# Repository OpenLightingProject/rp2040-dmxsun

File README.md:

# rp2040-dmxsun: A USB-DMX device based on RaspberryPi's RP2040 micro-controller with modular hardware

## What is it?

The rp2040-dmxsun is a multi-purpose DMX-512-A toolbox to control stage lighting systems. It's most common use-case is to transmit the DMX data generated on a PC, Raspberry Pi or similar in a format that the lighting fixtures on stage can understand. In the most simple case, it's an USB-DMX interface.

DMX-512-A works in networks called universes and each universe can contain up to 512 slots of data. dmxsun can transmit up to 16 universes, meaning you can control 8192 slots of DMX data at the same time.

Dmxsun is usually connected to its host via a single USB connection that also powers the device.
To the computer, the dmxsun device looks like a network card (it uses the CDC NCM interface) and the integrated DHCP-server assigns an IP-address to the host machine so they can talk to each other.

To find out dmxsun's IP address, have a look at your kernel log on Linux (run `dmesg`) or hover over the `Disconnect USB device` icon in Window's task bar or check the network device properties on macOS.

You can browse to this IP address in your web browser to access the integrated web server or you can send ArtNet or E1.31/sACN packets to the IP address to make dmxsun send this data as DMX data.

Furthermore, you can attach an nRF24 radio module to the base board to send or receive up to 4 universes wirelessly to or from another dmxsun device. That also means that the device can also work stand-alone, receiving DMX data from another dmxsun device and outputting it on local ports.

## Why is it called dmxsun?

The idea came when thinking about a suitable icon for the pages on the integrated web server. You can think about the dmxsun as being a central device and 16 rays of light coming out of it.

**Sun** could also be seen as an acronym for **s**ixteen **un**iverses :D

Maybe it's also because outdoor lighting technicians absolutely love the sun since they can perfectly set up their light show while the sun is shining bright ;)

## What does it look like?

The hardware consists of a base board into which the Raspberry Pi Pico-board plugs in to. To get a quick overview of the board's status, 8 RGB status LEDs are attached to the base board.

Attached to this base board can be 0 to 4 IO boards that carry the actual RS-485 drivers and XLR connectors:

If all 4 IO boards are attached to the base board, you can have 16 output ports fitting into 1U of an 19" rack:

## How is configuration data handled?

The complete configuration of the device, including IP address, patching and wireless configuration can be stored on any of the IO boards or on the base board.

When the device powers up, it scans the 4 IO board slots in order for connected boards and the configuration stored on them. As soon as a valid and non-disabled configuration is found, it is loaded and used. If no IO board has a valid configuration, it tries to load the config from the flash memory of the Pico board. If this also doesn't seem valid, a fallback configuration is applied.

The status LEDs on the base board indicate which IO boards have a valid configuration and which configuration is currently active.

All the configurations can be managed via the integrated web server.

## Where can I buy it?

Short answer: You can't. There is not (yet) a ready-made piece of hardware that can be bought and is ready to use. However, you are invited to build your own. Read on ;)

Longer answer: JLCPCB or a similar PCB factory. The schematics and PCB layout files are in the `hardware` folder (KiCad format) and you can send them to any PCB fab to have it produced for you. Then it's a bit of soldering on your side, plugging in a RaspberryPi Pico board and you're good to go.

If you just want to have a brief look at the schematics without cloning the repo and opening the files in KiCad, take a look at the kicad-export action: https://github.com/OpenLightingProject/rp2040-dmxsun/actions/workflows/kicad-exports.yml. It will generate a zip-archive containing all sort of PDFs.

**!!! Upcoming, incompatible hardware change: In the current schematics, we are using 256 byte large I2C-EEPROMs to store personality and configuration data. With the release of the Pico W and the need to store WiFi SSIDs and passwords, this will no longer be enough and the EEPROMs should provide 4096 byte in the future !!!**

## How can I try it out without spending much?

Very good question! All you need is a RaspberryPi Pico board, a microUSB cable and a PC, Laptop or RaspberryPi. You won't be able to actually control lighting fixtures, but you can get an idea of how this project works.

* Download the latest `UF2`-file (for example from here: https://github.com/OpenLightingProject/rp2040-dmxsun/actions/workflows/pico-build.yml) and flash it to your Pico board (see above)
* Wait until the board has rebooted and your PC has finished setting up the emulated network connection
* Find out the dmxsun's IP address as described in the [What is it?](#what-is-it)-section
* Open your web browser, browse to the IP address. You should see a web page with status information
* Using the navigation bar at the top, browse to `Console` and start changing values. Or fire up your favourite lighting control software (such as OLA or QLC+), configure it to send ArtNet or E1.31/sACN to the dmxsun's IP address and watch the values change in your web browser. It might seem laggy but that's only because the web interface only updates every second.
* If you're curious and have such devices, connect a logic analyzer or RS-485 driver to GPIOs 6 to 21. Those are the pins where the DMX data comes out. If you attach an RS-485-driver to one of those, you can also attach and control real fixtures.

## How do I compile the firmware?

If you just want to get started quickly find the most recent action run from the branch you're interested in, extract the attached artifact zip file (from https://github.com/OpenLightingProject/rp2040-dmxsun/actions/workflows/pico-build.yml ) and copy the rp2040-dmxsun.uf2 file to the Pico board when it's in bootloader mode.

Since this is a project that adheres to the guidelines set by Raspberry Pi for its pico-sdk (hopefully), you are best off following the detailed documentation at https://datasheets.raspberrypi.com/pico/getting-started-with-pico.pdf.

The build process will also build the React App for the integrated Web UI. For this to work, you will need to have NodeJS 14+ and NPM installed. React and all other JavaScript dependencies will be downloaded during the build, so make sure you are connected to the Internet.

With all dependencies installed, the following steps should suffice (example is for Linux, might differ for other OS):
```
git clone --recursive https://github.com/OpenLightingProject/rp2040-dmxsun.git
cd rp2040-dmxsun
mkdir build
cd build
cmake ..
make -j$(($(nproc)+1))
```
This should result in an `.uf2`-file being generated that you can flash to your Pico-board as described in Raspberry Pi's documentation.

**If you are seeing build errors, please make sure you are using pcio-sdk v1.5.0 (released 2023-02-11)**

## How does the data flow internally?

Dmxsun uses a pretty flexible architecture, consisting of mainly 24 DMX buffers acting as the main data storage. Data can come in via USB (either via the emulated Ethernet or some other, emulated protocol), wirelessly via the nRF24 module or from one input port and is then, depending on "patching" stored in one or more DMX buffers.

From there, again depending on "patching", the data is sent to one or more of the local DMX ports, to the nRF24 wireless module or to the host PC via Art-Net or E1.31/sACN.

The patching is currently fixed but will be made fully configurable in the future. The current patching works like this: Universes 1-16 from USB or emulated Ethernet go to internal DMX buffers 1-16 which go to the 16 local DMX ports. Additionally, the first 4 universes are also broadcast via the nRF24 module, should one be connected. Data coming in via the wireless module is sent to DMX buffers 5-8 and will as such appear on the local DMX ports 5-8.

## What are the upcoming features?

The best overview of planned features is to have a look at the GitHub issues: https://github.com/OpenLightingProject/rp2040-dmxsun/issues.

Since the hardware is modular, we do have the option to also support DMX input (currently work-in-progress) or universes with RDM support. There would also be the possibility to drive up to 6 WS2812b-based LED-strings instead of conventional DMX-512-A right off the board.

For the wireless part, mesh support is planned so you can add additional nodes forwarding the data when the wireless range is insufficient. It would also be great if we could talk to other, existing wireless DMX systems.

What might also help to make it easier to use is if dmxsun could emulate other, existing, USB DMX dongles. Then, it could also be used with other software that is not able to send Art-Net or E1.31/sACN but supports other dongles. The disadvantage here is that only a few dongles support more than 4 universes, while dmxsun supports 16.

As said above, the internal patching is hardcoded and cannot be changed by the user. This will change in the future, so that the current patching can be seen and changed in the integrated web interface.

## How is the project licensed?

This source code, schematics and board layouts is licensed under the Apache-2.0 license.

Parts of the original example code (`stdio_usb.*`, ...) is:

     * Copyright (c) 2020 Raspberry Pi (Trading) Ltd.
     * SPDX-License-Identifier: BSD-3-Clause

Parts taken and modified from TinyUSB (`tusb_config.h`, `usb_descriptors.c`) is:

     * The MIT License (MIT)
     * Copyright (c) 2019 Ha Thach (tinyusb.org)

This project proudly uses the following libraries and thanks the respective developers for their amazing work:
* [jsoncpp](https://github.com/open-source-parsers/jsoncpp), MIT license
* [libb64](https://github.com/libb64/libb64), Public domain
* [lwIP](https://savannah.nongnu.org/projects/lwip/), Modified BSD License
* [Pico-DMX](https://github.com/jostlowe/Pico-DMX), BSD 3-Clause "New" or "Revised" License
* [RF24, RF24Network and RF24Mesh](https://github.com/nRF24/RF24), GPL-2.0. Since this is not compatible with our Apache-2.0 license, this dependency will be removed in the future. dmxsun was GPL-licensed in the past
* [snappy](https://github.com/google/snappy), The 3-Clause BSD License

And for the integrated Web UI:
* [React](https://reactjs.org/), MIT license
* [Bootstrap](https://getbootstrap.com/), MIT license
* [Chart.js](https://www.chartjs.org/), MIT license
* [couch64](https://www.npmjs.com/package/couch64), CC-BY-SA
* [snappyjs](https://github.com/zhipeng-jia/snappyjs), MIT license
* [react-input-slider](https://github.com/swiftcarrot/react-input-slider), MIT license

## What else do I need to know?

If you attach an nRF24-board, you yourself are responsible to make sure you don't violate any local laws or regulations. Not all channels and transmit powers that the nRF24 module can use may be allowed to be used in your area. The Open Lighting Project cannot be held responsible should you break the law by using this project's hardware and/or software. Also, we did not run any EMC tests on the hardware. It might not be legal to operate the board without FCC, CE or similar certification, depending on where you live.

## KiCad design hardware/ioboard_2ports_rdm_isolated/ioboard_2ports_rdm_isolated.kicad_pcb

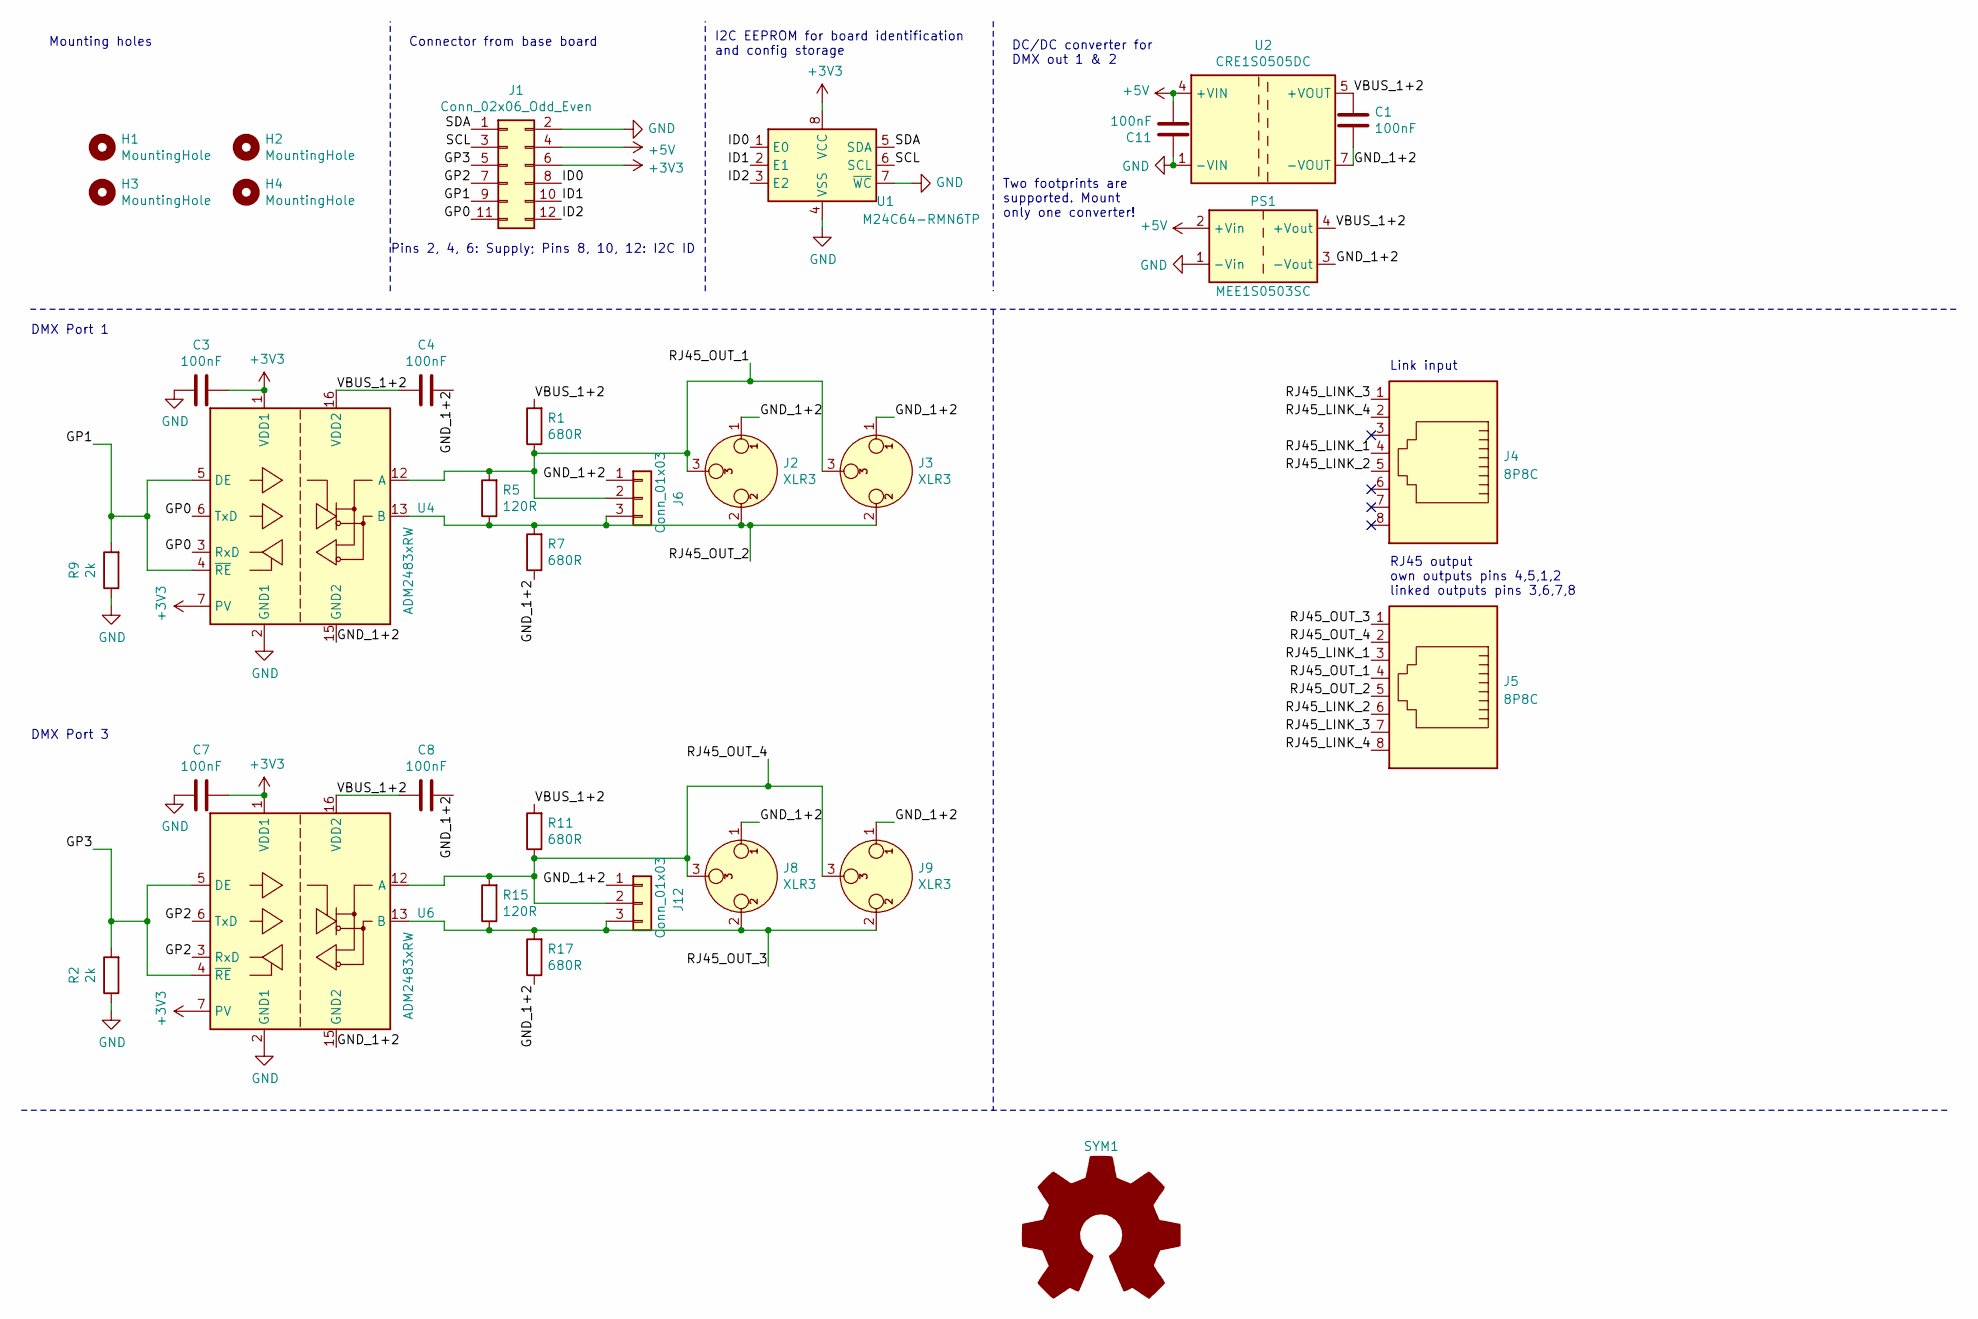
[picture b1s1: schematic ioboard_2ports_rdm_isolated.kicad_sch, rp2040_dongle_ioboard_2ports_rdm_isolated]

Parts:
C1, C3, C4, C7, C8, C11: 100nF; C_0603_1608Metric; LCSC C14663
H1, H2, H3, H4: MountingHole; MountingHole_3.2mm_M3
J1: Conn_02x06_Odd_Even; PinHeader_2x06_P2.54mm_Vertical
J2, J8: XLR3; Jack_XLR_Neutrik_NC3FAAH_Horizontal
J3, J9: XLR3; Jack_XLR_Neutrik_NC3FD-H_Horizontal
J4, J5: 8P8C; RJ45_Sparkfun
J6, J12: Conn_01x03; PinHeader_1x03_P2.54mm_Vertical
PS1: MEE1S0503SC; Converter_DCDC_Murata_CRE1xxxxxx3C_THT
R1, R7, R11, R17: 680R; R_0603_1608Metric_Pad0.98x0.95mm_HandSolder; LCSC C23228
R2, R9: 2k; R_0805_2012Metric_Pad1.20x1.40mm_HandSolder; LCSC C17604
R5, R15: 120R; R_0603_1608Metric_Pad0.98x0.95mm_HandSolder; LCSC C22787
SYM1: Logo_Open_Hardware_Large; OSHW-Logo2_14.6x12mm_SilkScreen
U1: M24C64-RMN6TP; SOIC-8_3.9x4.9mm_P1.27mm; LCSC C79988
U2: CRE1S0505DC; Converter_DCDC_Murata_CRE1xxxxxxDC_THT
U4, U6: ADM2483xRW; SOIC-16W_7.5x10.3mm_P1.27mm; LCSC C9637

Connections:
+3V3: C3.1, C7.1, J1.6, U1.8 (VCC), U4.1 (VDD1), U4.7 (PV), U6.1 (VDD1), U6.7 (PV)
+5V: C11.1, J1.4, PS1.2 (+Vin), U2.4 (+VIN)
/GND_1+2: C1.1, C4.1, C8.1, J2.1, J3.1, J6.1, J8.1, J9.1, J12.1, PS1.3 (-Vout), R7.1, R17.1, U2.7 (-VOUT), U4.9 (GND2), U4.15 (GND2), U6.9 (GND2), U6.15 (GND2)
/GP0: J1.11, U4.3 (RxD), U4.6 (TxD)
/GP1: J1.9, R9.2, U4.4 (~RE), U4.5 (DE)
/GP2: J1.7, U6.3 (RxD), U6.6 (TxD)
/GP3: J1.5, R2.2, U6.4 (~RE), U6.5 (DE)
/ID0: J1.8, U1.1 (E0)
/ID1: J1.10, U1.2 (E1)
/ID2: J1.12, U1.3 (E2)
/RJ45_LINK_1: J4.4, J5.3
/RJ45_LINK_2: J4.5, J5.6
/RJ45_LINK_3: J4.1, J5.7
/RJ45_LINK_4: J4.2, J5.8
/RJ45_OUT_1: J2.3, J3.3, J5.4, J6.2, R1.1, R5.2, U4.12 (A)
/RJ45_OUT_2: J2.2, J3.2, J5.5, J6.3, R5.1, R7.2, U4.13 (B)
/RJ45_OUT_3: J5.1, J8.2, J9.2, J12.3, R15.1, R17.2, U6.13 (B)
/RJ45_OUT_4: J5.2, J8.3, J9.3, J12.2, R11.1, R15.2, U6.12 (A)
/SCL: J1.3, U1.6 (SCL)
/SDA: J1.1, U1.5 (SDA)
/VBUS_1+2: C1.2, C4.2, C8.2, PS1.4 (+Vout), R1.2, R11.2, U2.5 (+VOUT), U4.16 (VDD2), U6.16 (VDD2)
GND: C3.2, C7.2, C11.2, J1.2, PS1.1 (-Vin), R2.1, R9.1, U1.4 (VSS), U1.7 (~WC), U2.1 (-VIN), U4.2 (GND1), U4.8 (GND1), U6.2 (GND1), U6.8 (GND1)

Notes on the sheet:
I2C EEPROM for board identification and config storage
DC/DC converter for DMX out 1 & 2
DMX Port 3
DMX Port 1
Pins 2, 4, 6: Supply; Pins 8, 10, 12: I2C ID
Connector from base board
Mounting holes
Link input
RJ45 output own outputs pins 4,5,1,2 linked outputs pins 3,6,7,8
Two footprints are supported. Mount only one converter!

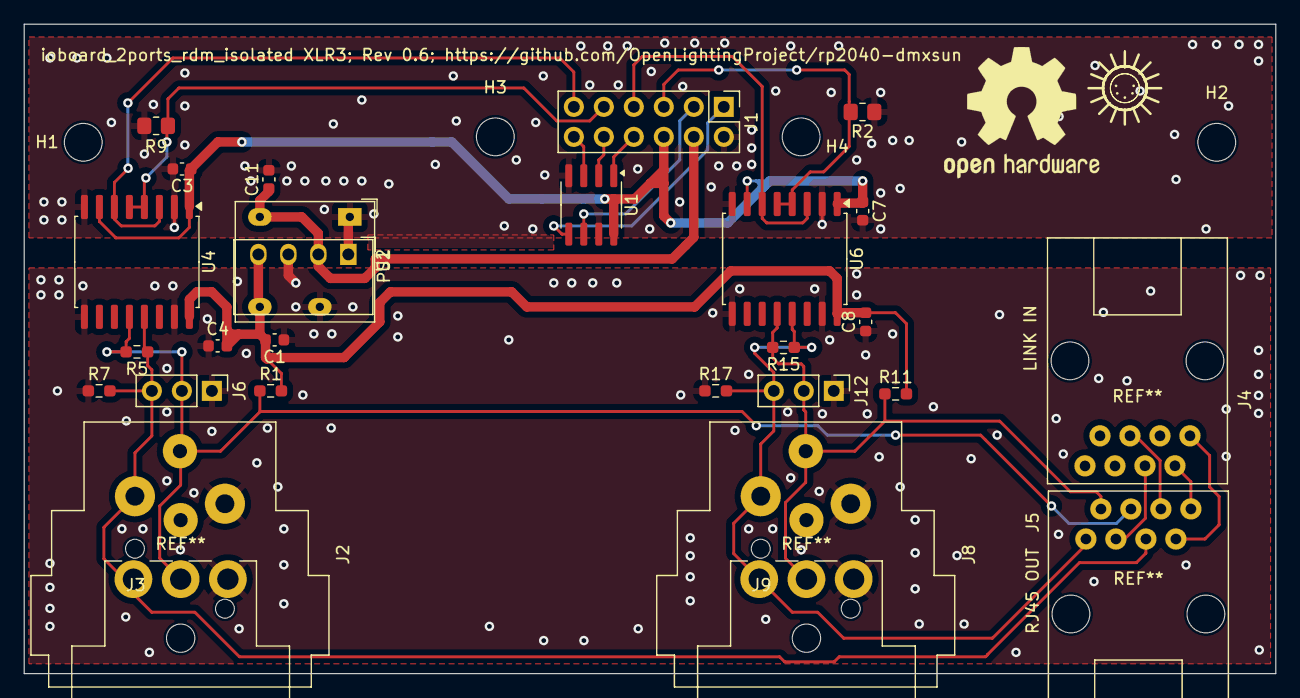
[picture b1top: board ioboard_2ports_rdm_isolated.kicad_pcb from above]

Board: 2 copper layers, 106.0 x 55.0 mm, 33 parts (0 on the bottom side), 22 nets.

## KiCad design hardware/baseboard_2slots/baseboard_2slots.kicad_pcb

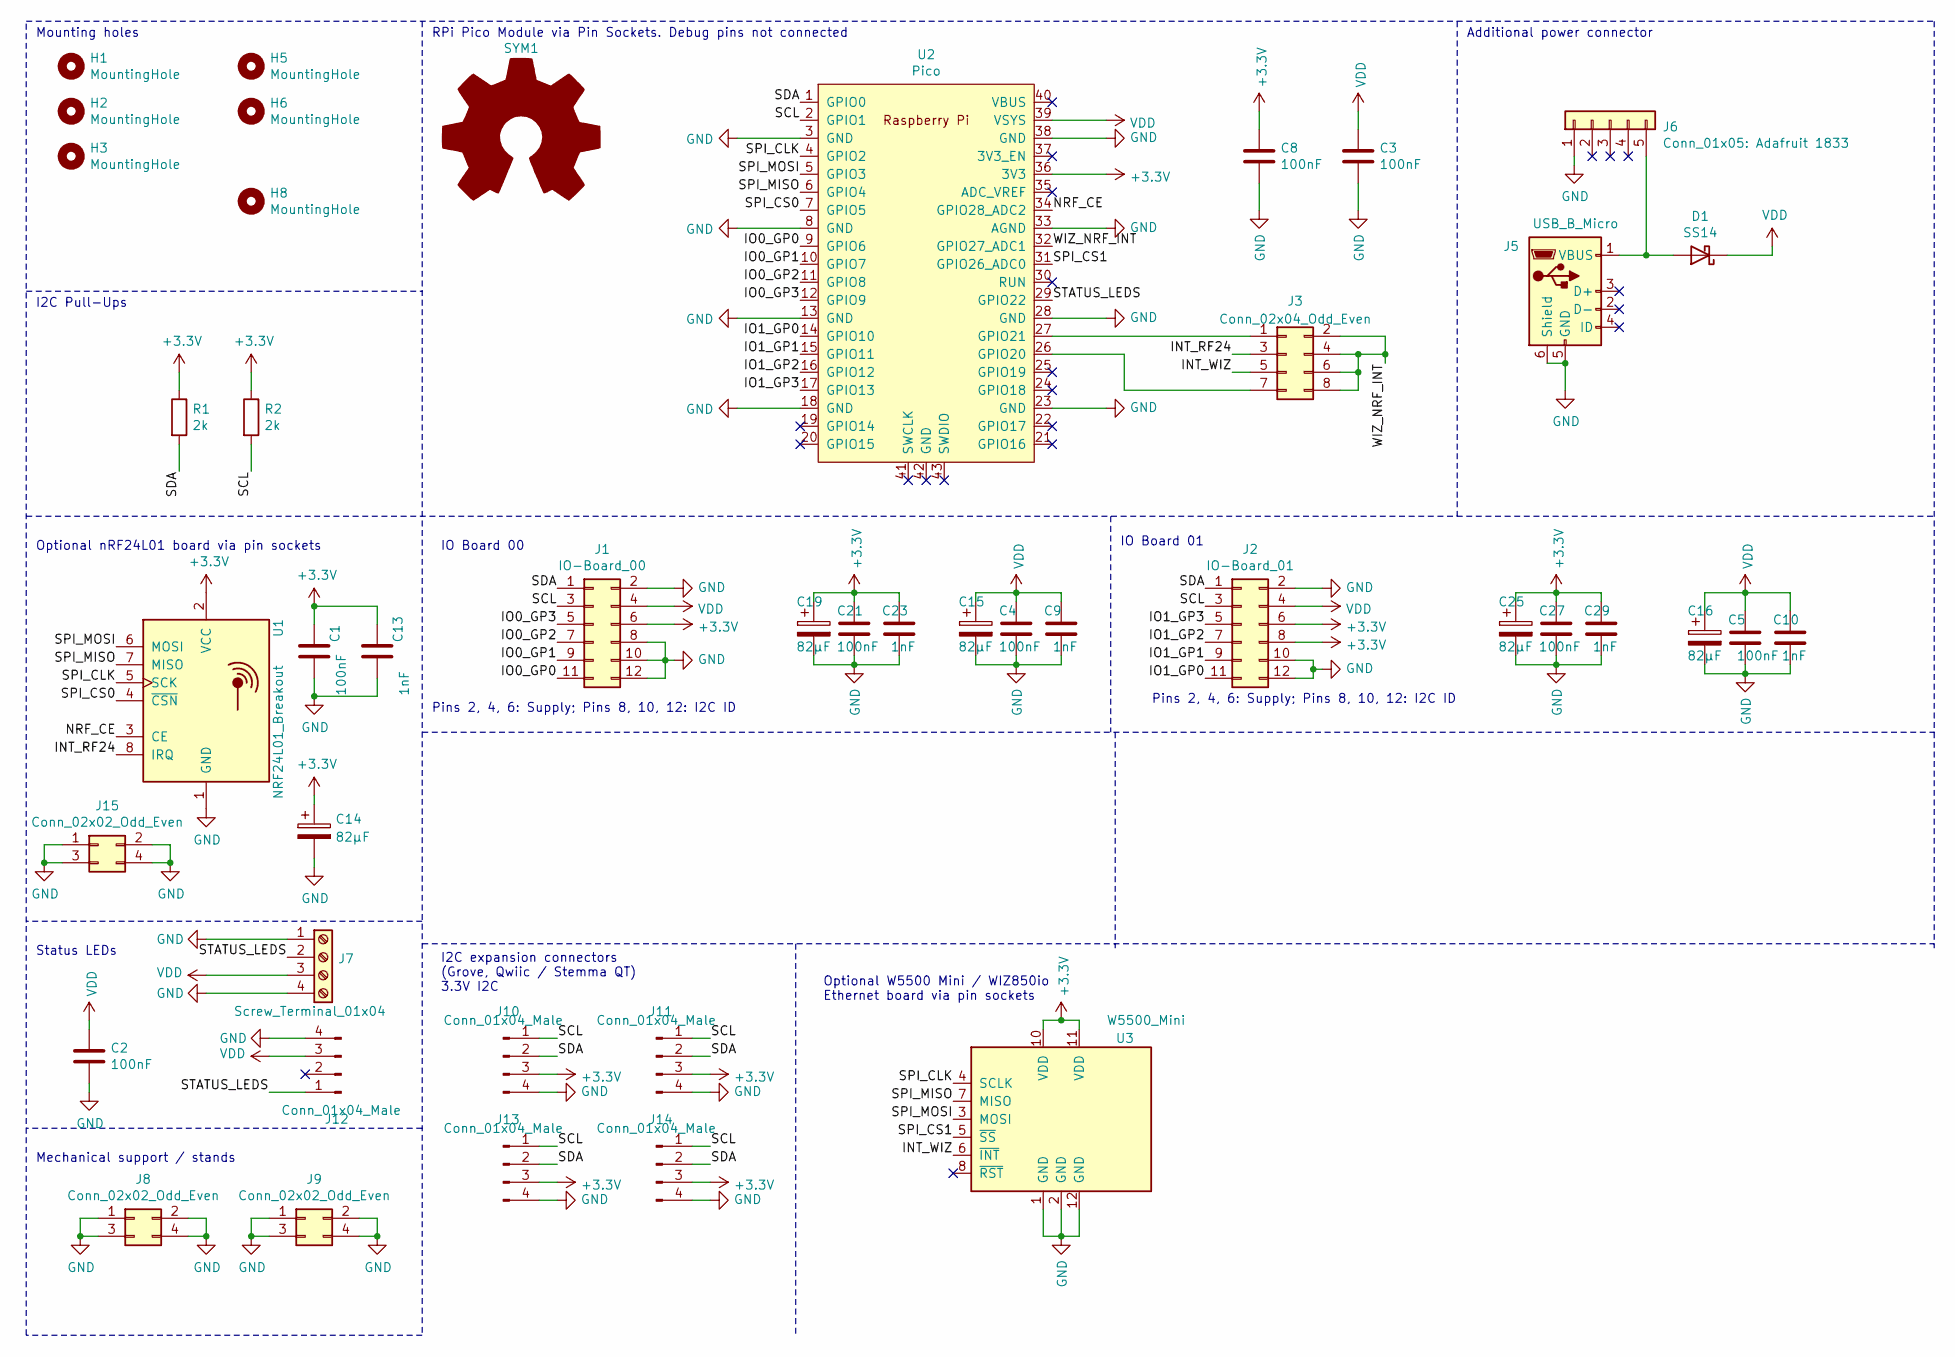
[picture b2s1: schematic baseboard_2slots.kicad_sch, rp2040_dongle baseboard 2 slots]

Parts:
C1, C2, C3, C4, C5, C8, C21, C27: 100nF; C_0603_1608Metric; LCSC C14663
C9, C10, C13, C23, C29: 1nF; C_0603_1608Metric; LCSC C1588
C14, C15, C16, C19, C25: 82µF; CP_Radial_D6.3mm_P2.50mm
D1: SS14; D_SMA; LCSC C2480
H1, H2, H3, H5, H6, H8: MountingHole; MountingHole_3.2mm_M3
J1: IO-Board_00; PinSocket_2x06_P2.54mm_Vertical
J2: IO-Board_01; PinSocket_2x06_P2.54mm_Vertical
J3: Conn_02x04_Odd_Even; PinHeader_2x04_P2.54mm_Vertical
J5: USB_B_Micro; USB_Micro-B_Wuerth_629105150521
J6: Conn_01x05: Adafruit 1833; PinHeader_1x05_P2.54mm_Vertical
J7: Screw_Terminal_01x04; TerminalBlock_Altech_AK300-4_P5.00mm
J8, J9: Conn_02x02_Odd_Even; PinHeader_2x02_P2.54mm_Vertical
J10, J11, J12: Conn_01x04_Male; NS-Tech_Grove_1x04_P2mm_Vertical
J13, J14: Conn_01x04_Male; JST_SH_BM04B-SRSS-TB_1x04-1MP_P1.00mm_Vertical
J15: Conn_02x02_Odd_Even; PinSocket_2x02_P2.54mm_Vertical
R1, R2: 2k; R_0805_2012Metric_Pad1.20x1.40mm_HandSolder; LCSC C17604
SYM1: Logo_Open_Hardware_Large; OSHW-Logo2_14.6x12mm_SilkScreen
U1: NRF24L01_Breakout; nRF24L01_Breakout
U2: Pico; RPi_Pico_SMD_TH
U3: W5500_Mini

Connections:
+3.3V: C1.1, C8.1, C13.1, C14.1, C19.1, C21.1, C23.1, C25.1, C27.1, C29.1, J1.6, J2.6, J2.8, J10.3, J11.3, J13.3, J14.3, R1.1, R2.1, U1.2 (VCC), U2.36 (3V3), U3.10 (VDD), U3.11 (VDD)
/INT_RF24: J3.3, U1.8 (IRQ)
/INT_WIZ: J3.5, U3.6 (~INT)
/IO0_GP0: J1.11, U2.9 (GPIO6)
/IO0_GP1: J1.9, U2.10 (GPIO7)
/IO0_GP2: J1.7, U2.11 (GPIO8)
/IO0_GP3: J1.5, U2.12 (GPIO9)
/IO1_GP0: J2.11, U2.14 (GPIO10)
/IO1_GP1: J2.9, U2.15 (GPIO11)
/IO1_GP2: J2.7, U2.16 (GPIO12)
/IO1_GP3: J2.5, U2.17 (GPIO13)
/NRF_CE: U1.3 (CE), U2.34 (GPIO28_ADC2)
/SCL: J1.3, J2.3, J10.1, J11.1, J13.1, J14.1, R2.2, U2.2 (GPIO1)
/SDA: J1.1, J2.1, J10.2, J11.2, J13.2, J14.2, R1.2, U2.1 (GPIO0)
/SPI_CLK: U1.5 (SCK), U2.4 (GPIO2), U3.4 (SCLK)
/SPI_CS0: U1.4 (~CSN), U2.7 (GPIO5)
/SPI_CS1: U2.31 (GPIO26_ADC0), U3.5 (~SS)
/SPI_MISO: U1.7 (MISO), U2.6 (GPIO4), U3.7 (MISO)
/SPI_MOSI: U1.6 (MOSI), U2.5 (GPIO3), U3.3 (MOSI)
/STATUS_LEDS: J7.2, J12.1, U2.29 (GPIO22)
/WIZ_NRF_INT: J3.2, J3.4, J3.6, J3.8, U2.32 (GPIO27_ADC1)
GND: C1.2, C2.2, C3.2, C4.2, C5.2, C8.2, C9.2, C10.2, C13.2, C14.2, C15.2, C16.2, C19.2, C21.2, C23.2, C25.2, C27.2, C29.2, J1.2, J1.8, J1.10, J1.12, J2.2, J2.10, J2.12, J5.5 (GND), J5.6 (Shield), J6.1, J7.1, J7.4, J8.1, J8.2, J8.3, J8.4, J9.1, J9.2, J9.3, J9.4, J10.4, J11.4, J12.4, J13.4, J14.4, J15.1, J15.2, J15.3, J15.4, U1.1 (GND), U2.3 (GND), U2.8 (GND), U2.13 (GND), U2.18 (GND), U2.23 (GND), U2.28 (GND), U2.33 (AGND), U2.38 (GND), U3.1 (GND), U3.2 (GND), U3.12 (GND)
unnamed: D1.2 (A), J5.1 (VBUS), J6.5
unnamed: J3.1, U2.27 (GPIO21)
unnamed: J3.7, U2.26 (GPIO20)
VDD: C2.1, C3.1, C4.1, C5.1, C9.1, C10.1, C15.1, C16.1, D1.1 (K), J1.4, J2.4, J7.3, J12.3, U2.39 (VSYS)

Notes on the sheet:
Pins 2, 4, 6: Supply; Pins 8, 10, 12: I2C ID
Additional power connector
Mounting holes
RPi Pico Module via Pin Sockets. Debug pins not connected
IO Board 00
I2C Pull-Ups
Status LEDs
Optional nRF24L01 board via pin sockets
IO Board 01
Mechanical support / stands
I2C expansion connectors (Grove, Qwiic / Stemma QT) 3.3V I2C
Optional W5500 Mini / WIZ850io Ethernet board via pin sockets

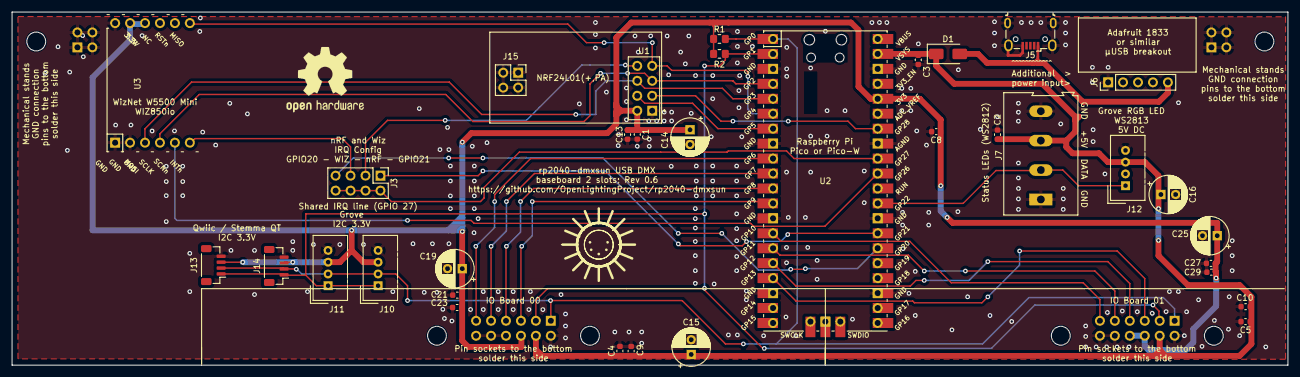
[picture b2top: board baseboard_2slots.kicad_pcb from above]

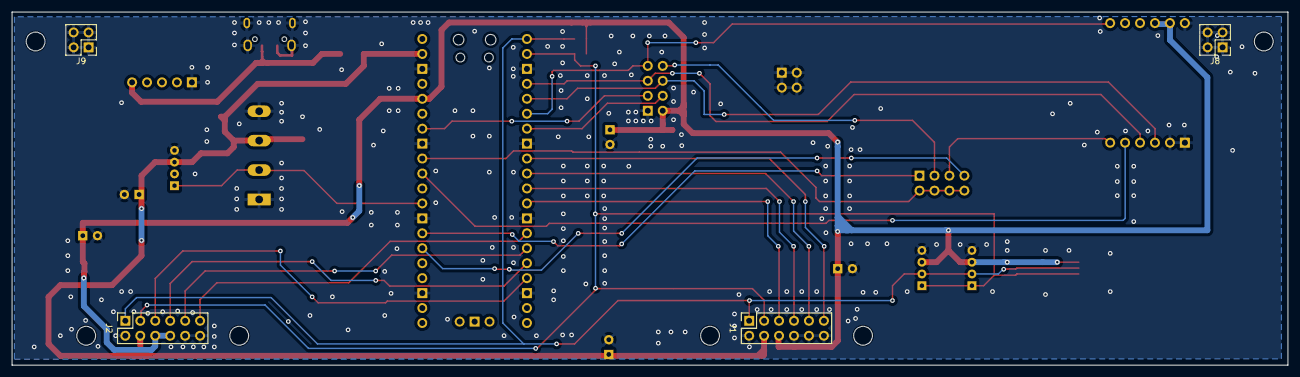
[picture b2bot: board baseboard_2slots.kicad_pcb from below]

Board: 2 copper layers, 216.8 x 60.0 mm, 45 parts (4 on the bottom side), 26 nets.

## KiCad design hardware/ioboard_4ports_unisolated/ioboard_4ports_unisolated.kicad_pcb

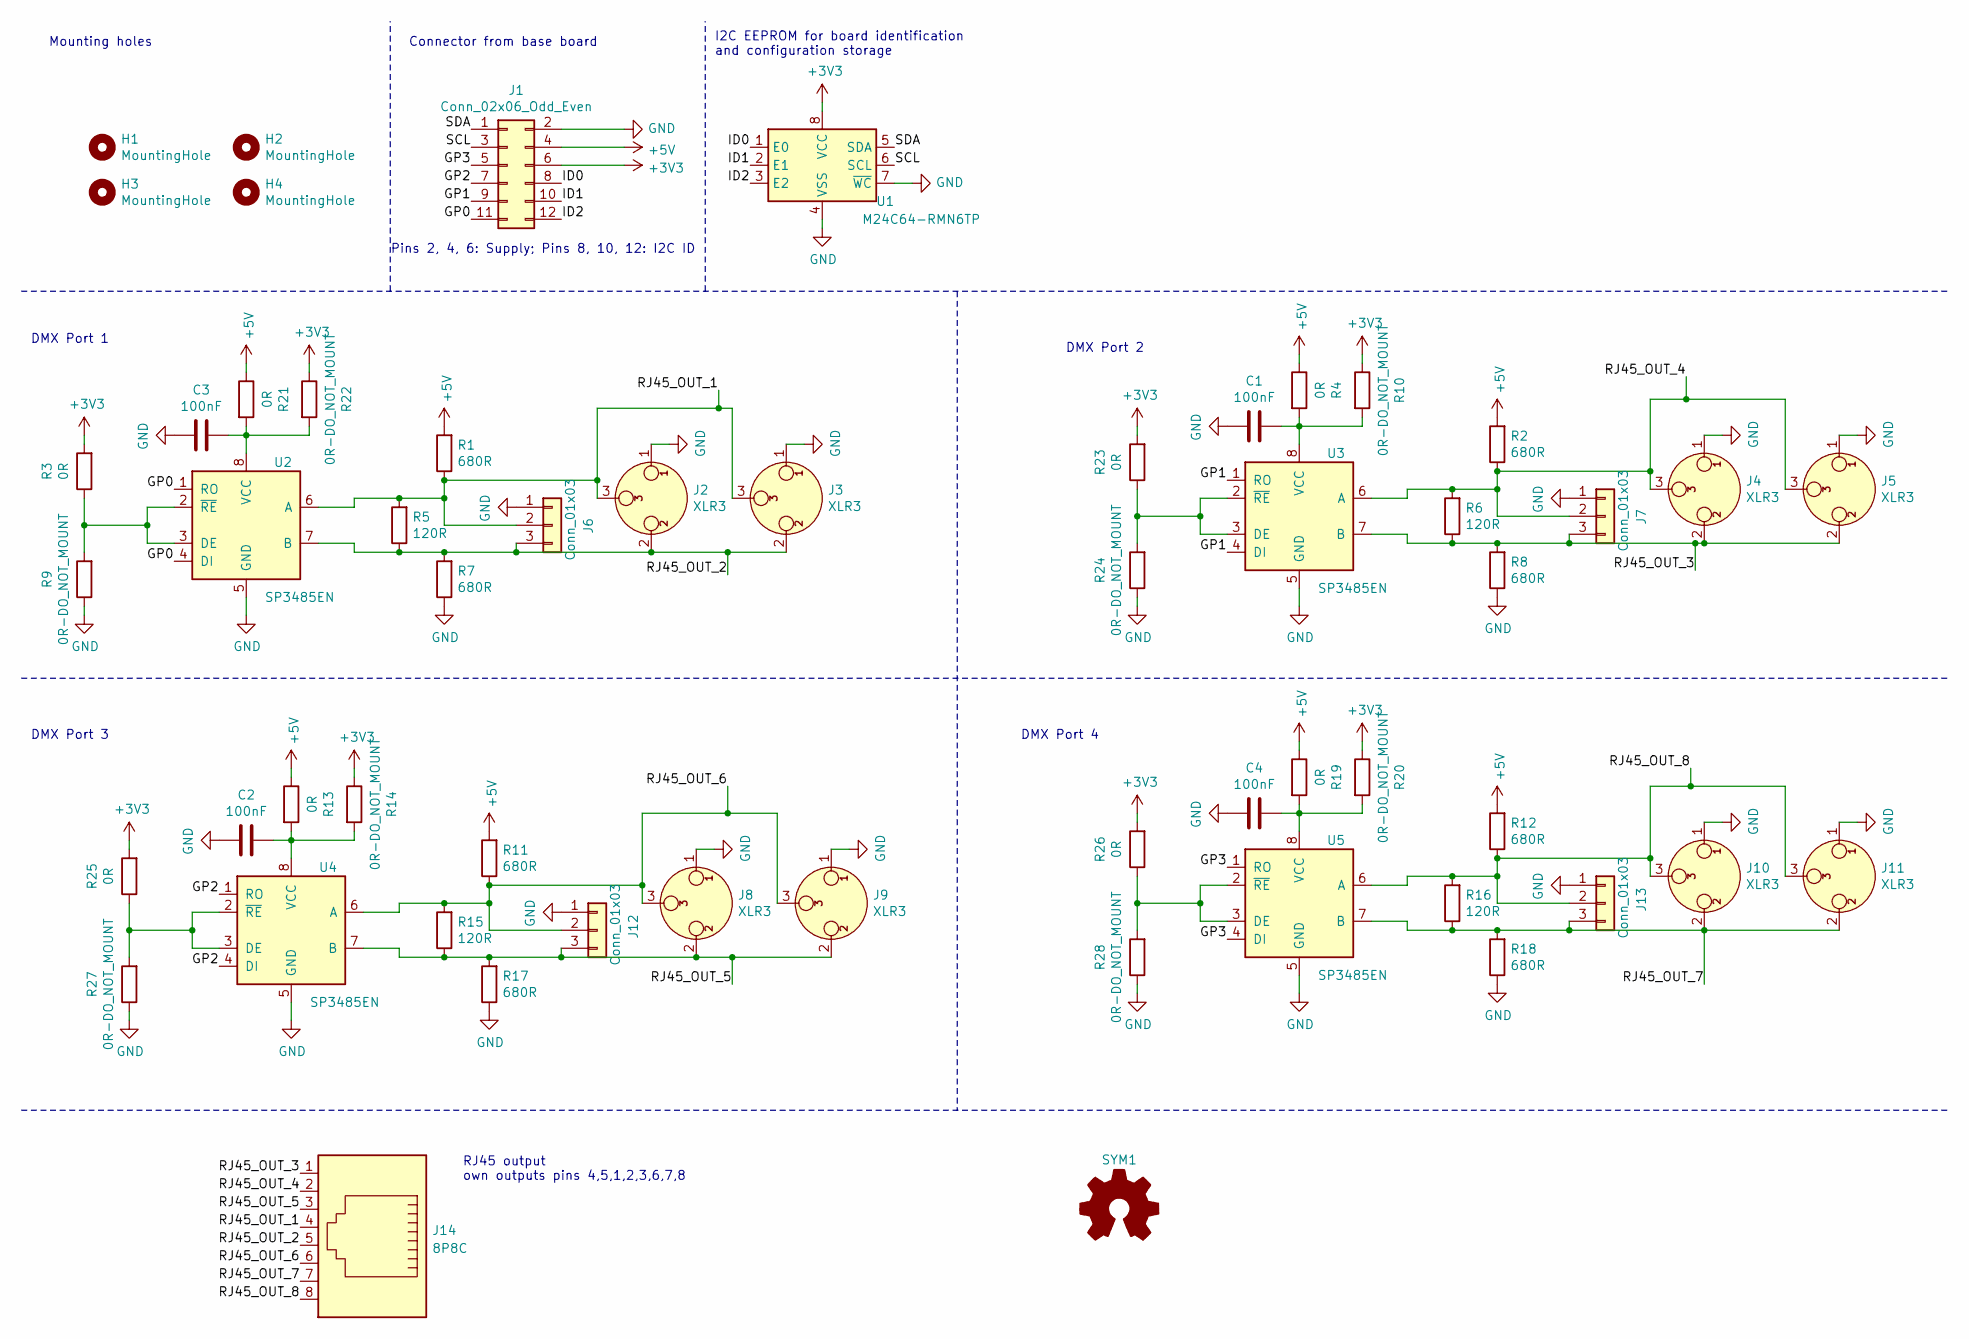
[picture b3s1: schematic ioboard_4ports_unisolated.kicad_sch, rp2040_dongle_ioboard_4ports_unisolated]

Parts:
C1, C2, C3, C4: 100nF; C_0603_1608Metric; LCSC C14663
H1, H2, H3, H4: MountingHole; MountingHole_3.2mm_M3
J1: Conn_02x06_Odd_Even; PinHeader_2x06_P2.54mm_Vertical
J2, J4, J8, J10: XLR3; Jack_XLR_Neutrik_NC3FAAH_Horizontal
J3, J5, J9, J11: XLR3; Jack_XLR_Neutrik_NC3FD-H_Horizontal
J6, J7, J12, J13: Conn_01x03; PinHeader_1x03_P2.54mm_Vertical
J14: 8P8C; RJ45_Sparkfun
R1, R2, R7, R8, R11, R12, R17, R18: 680R; R_0603_1608Metric_Pad0.98x0.95mm_HandSolder; LCSC C23228
R3, R4, R13, R19, R21, R23, R25, R26: 0R; R_0805_2012Metric_Pad1.20x1.40mm_HandSolder; LCSC C17477
R5, R6, R15, R16: 120R; R_0603_1608Metric_Pad0.98x0.95mm_HandSolder; LCSC C22787
R9, R10, R14, R20, R22, R24, R27, R28: 0R-DO_NOT_MOUNT; R_0805_2012Metric_Pad1.20x1.40mm_HandSolder; LCSC C17477
SYM1: Logo_Open_Hardware_Small; OSHW-Logo2_7.3x6mm_SilkScreen
U1: M24C64-RMN6TP; SOIC-8_3.9x4.9mm_P1.27mm; LCSC C79988
U2, U3, U4, U5: SP3485EN; SOIC-8_3.9x4.9mm_P1.27mm; LCSC C8963

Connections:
+3V3: J1.6, R3.2, R10.1, R14.1, R20.1, R22.1, R23.2, R25.2, R26.2, U1.8 (VCC)
+5V: J1.4, R1.2, R2.2, R4.1, R11.2, R12.2, R13.1, R19.1, R21.1
/GP0: J1.11, U2.1 (RO), U2.4 (DI)
/GP1: J1.9, U3.1 (RO), U3.4 (DI)
/GP2: J1.7, U4.1 (RO), U4.4 (DI)
/GP3: J1.5, U5.1 (RO), U5.4 (DI)
/ID0: J1.8, U1.1 (E0)
/ID1: J1.10, U1.2 (E1)
/ID2: J1.12, U1.3 (E2)
/RJ45_OUT_1: J2.3, J3.3, J6.2, J14.4, R1.1, R5.2, U2.6 (A)
/RJ45_OUT_2: J2.2, J3.2, J6.3, J14.5, R5.1, R7.2, U2.7 (B)
/RJ45_OUT_3: J4.2, J5.2, J7.3, J14.1, R6.1, R8.2, U3.7 (B)
/RJ45_OUT_4: J4.3, J5.3, J7.2, J14.2, R2.1, R6.2, U3.6 (A)
/RJ45_OUT_5: J8.2, J9.2, J12.3, J14.3, R15.1, R17.2, U4.7 (B)
/RJ45_OUT_6: J8.3, J9.3, J12.2, J14.6, R11.1, R15.2, U4.6 (A)
/RJ45_OUT_7: J10.2, J11.2, J13.3, J14.7, R16.1, R18.2, U5.7 (B)
/RJ45_OUT_8: J10.3, J11.3, J13.2, J14.8, R12.1, R16.2, U5.6 (A)
/SCL: J1.3, U1.6 (SCL)
/SDA: J1.1, U1.5 (SDA)
GND: C1.2, C2.2, C3.2, C4.2, J1.2, J2.1, J3.1, J4.1, J5.1, J6.1, J7.1, J8.1, J9.1, J10.1, J11.1, J12.1, J13.1, R7.1, R8.1, R9.1, R17.1, R18.1, R24.1, R27.1, R28.1, U1.4 (VSS), U1.7 (~WC), U2.5 (GND), U3.5 (GND), U4.5 (GND), U5.5 (GND)
unnamed: R3.1, R9.2, U2.2 (~RE), U2.3 (DE)
unnamed: C3.1, R21.2, R22.2, U2.8 (VCC)
unnamed: R23.1, R24.2, U3.2 (~RE), U3.3 (DE)
unnamed: C1.1, R4.2, R10.2, U3.8 (VCC)
unnamed: R25.1, R27.2, U4.2 (~RE), U4.3 (DE)
unnamed: C2.1, R13.2, R14.2, U4.8 (VCC)
unnamed: R26.1, R28.2, U5.2 (~RE), U5.3 (DE)
unnamed: C4.1, R19.2, R20.2, U5.8 (VCC)

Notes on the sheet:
DMX Port 1
RJ45 output own outputs pins 4,5,1,2,3,6,7,8
DMX Port 4
I2C EEPROM for board identification and configuration storage
DMX Port 2
Connector from base board
DMX Port 3
Pins 2, 4, 6: Supply; Pins 8, 10, 12: I2C ID
Mounting holes

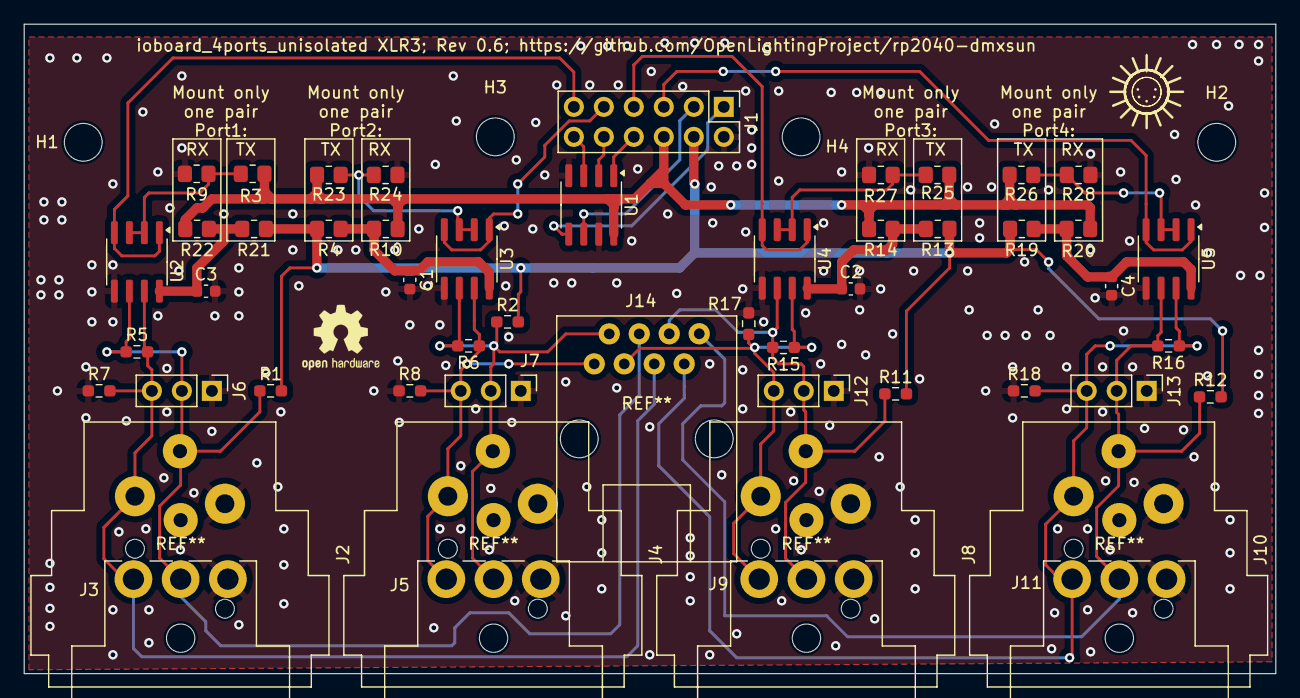
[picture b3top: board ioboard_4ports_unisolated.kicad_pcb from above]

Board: 2 copper layers, 106.0 x 55.0 mm, 56 parts (0 on the bottom side), 28 nets.
